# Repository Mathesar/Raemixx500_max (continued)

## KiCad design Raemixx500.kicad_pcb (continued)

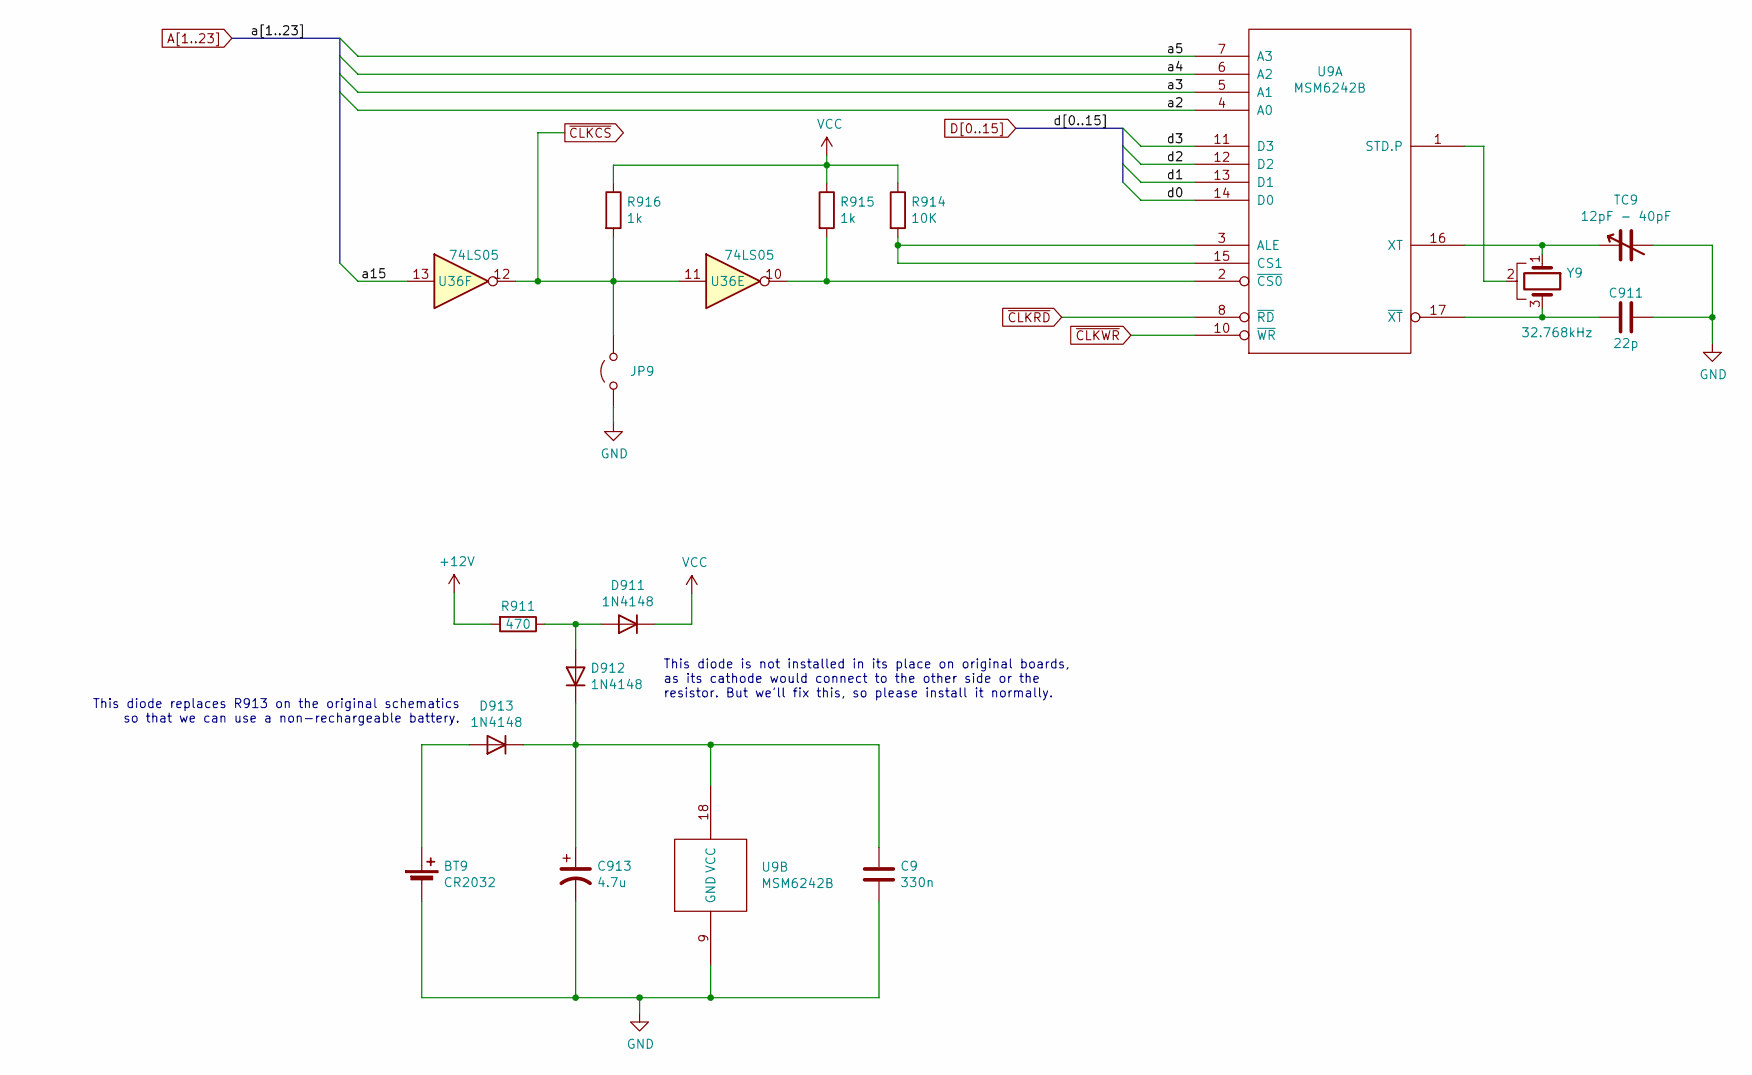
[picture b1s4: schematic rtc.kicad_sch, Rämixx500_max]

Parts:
BT9: CR2032; Battery_Holder_Coin_2032_BS-7; MFG Part Num 122-2420-GR; Mouser 122-2420-GR
C9: 330n; C_Axial_L6.3mm_D2.5mm_P10.16mm; MFG Part Num C440C334K5R5TA7200; Mouser 80-C440C334K5R-TR
C911: 22p; C_Axial_L6.3mm_D2.5mm_P10.16mm; MFG Part Num C410C220J1G5TA; Mouser 80-C410C220J1G
C913: 4.7u; CP_Radial_D8.0mm_P5.00mm; MFG Part Num ECA-2AM4R7B; Mouser 667-ECA-2AM4R7B
D911, D912, D913: 1N4148; D_DO-35_SOD27_P12.70mm_Horizontal; MFG Part Num 1N4148TR; Mouser 512-1N4148TR
JP9: Jumper_2_Open; Jumper2-Open; MFG Part Num SKIP
R911: 470; R_Axial_DIN0309_L9.0mm_D3.2mm_P12.70mm_Horizontal; MFG Part Num MFR-25FBF52-470R; Mouser 603-MFR-25FBF52-470R
R914: 10K; R_Axial_DIN0309_L9.0mm_D3.2mm_P12.70mm_Horizontal; MFG Part Num MFR-25FBF52-10K; Mouser 603-MFR-25FBF52-10K
R915, R916: 1k; R_Axial_DIN0309_L9.0mm_D3.2mm_P12.70mm_Horizontal; MFG Part Num MFR-25FBF52-1K; Mouser 603-MFR-25FBF52-1K
TC9: 12pF - 40pF; VariCap; MFG Part Num JML06-1 / 40PF / YELLOW
U9: MSM6242B; DIP-18_W7.62mm_Socket_LongPads; MFG Part Num 4818-3000-CP; Mouser 517-4818-3000-CP
U36: 74LS05; DIP-14_W7.62mm_LongPads; MFG Part Num SN74LS05N; Mouser 595-SN74LS05N
Y9: 32.768kHz; Crystal_RTC; MFG Part Num ECS-.327-12.5-13X; Mouser 520-TFC2X6-X

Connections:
+12V: R911.2; also elsewhere on the board
A2: U9.4 (A0); also elsewhere on the board
A3: U9.5 (A1); also elsewhere on the board
A4: U9.6 (A2); also elsewhere on the board
A5: U9.7 (A3); also elsewhere on the board
A15: U36.13; also elsewhere on the board
D0: U9.14 (D0); also elsewhere on the board
D1: U9.13 (D1); also elsewhere on the board
D2: U9.12 (D2); also elsewhere on the board
D3: U9.11 (D3); also elsewhere on the board
GND: BT9.2 (-), C9.2, C911.1, C913.2, JP9.1 (A), TC9.2, U9.9 (GND); also elsewhere on the board
unnamed: BT9.1 (+), D913.2 (A)
unnamed: D911.2 (A), D912.2 (A), R911.1
unnamed: C9.1, C913.1, D912.1 (K), D913.1 (K), U9.18 (VCC)
unnamed: R914.2, U9.3 (ALE), U9.15 (CS1)
unnamed: U9.1 (STD.P), Y9.2
unnamed: TC9.1, U9.16 (XT), Y9.1
unnamed: R915.2, U9.2 (~CS0), U36.10
unnamed: C911.2, U9.17 (~XT), Y9.3
VCC: D911.1 (K), R914.1, R915.1, R916.1; also elsewhere on the board
~CLKCS: JP9.2 (B), R916.2, U36.11, U36.12; also elsewhere on the board
~CLKRD: U9.8 (~RD); also elsewhere on the board
~CLKWR: U9.10 (~WR); also elsewhere on the board

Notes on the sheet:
This diode is not installed in its place on original boards, as its cathode would connect to the other side or the resistor. But we'll fix this, so please install it normally.
This diode replaces R913 on the original schematics so that we can use a non-rechargeable battery.

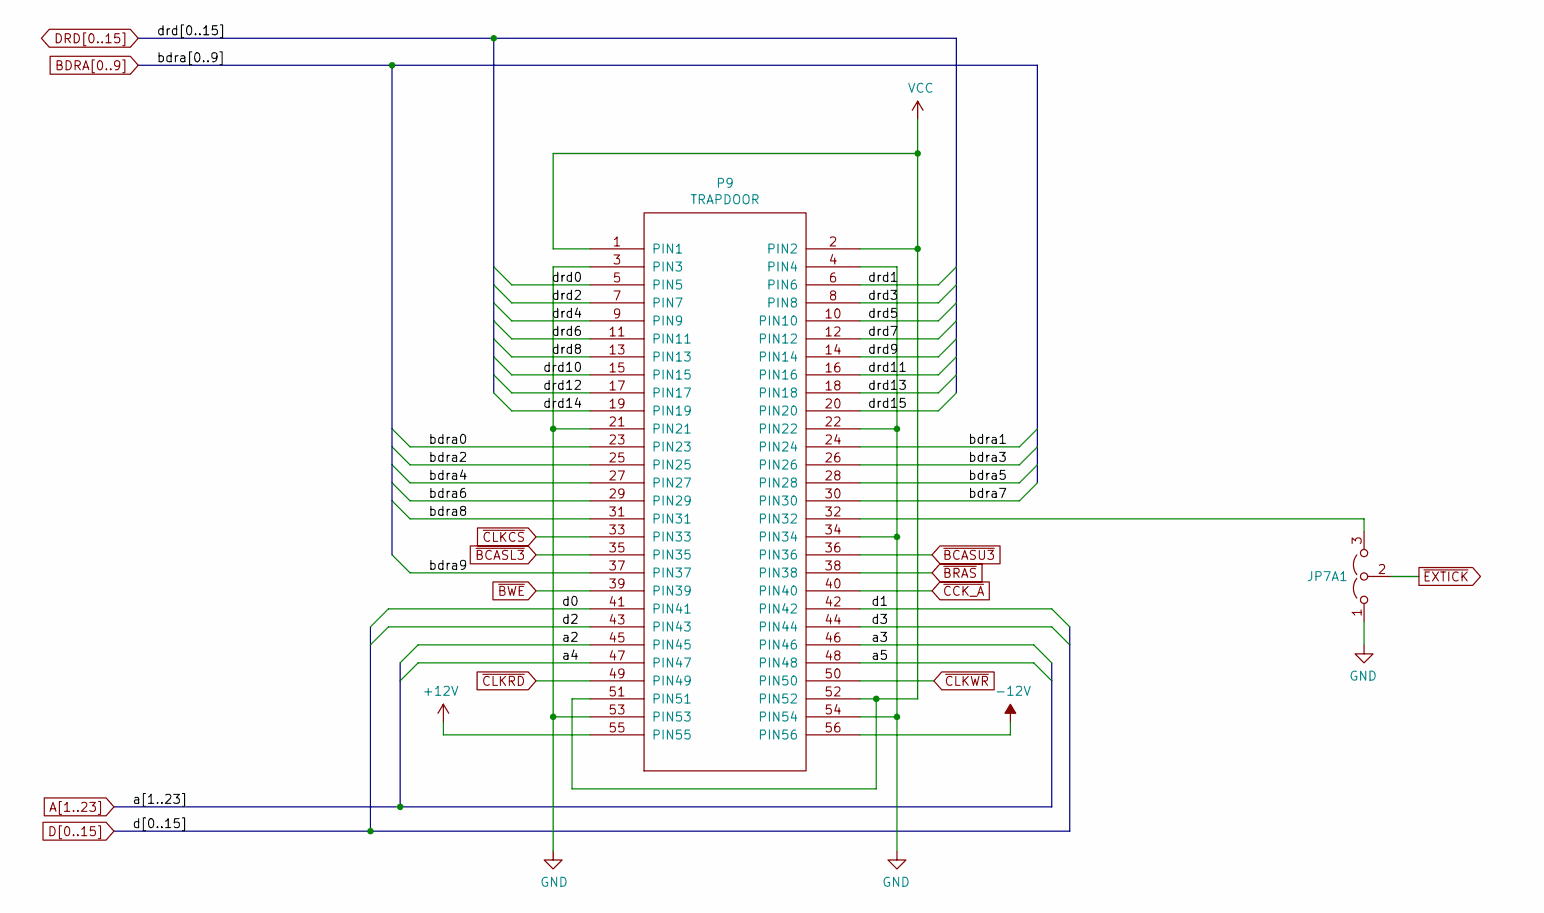
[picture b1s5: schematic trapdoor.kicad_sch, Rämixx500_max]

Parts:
JP7A1: Jumper_3_Open; Jumper3-Open; MFG Part Num SKIP
P9: TRAPDOOR; Trapdoor; MFG Part Num PH2RA-80-UA; Mouser 737-PH2RA-80-UA

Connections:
+12V: P9.55 (PIN55); also elsewhere on the board
-12V: P9.56 (PIN56); also elsewhere on the board
A2: P9.45 (PIN45); also elsewhere on the board
A3: P9.46 (PIN46); also elsewhere on the board
A4: P9.47 (PIN47); also elsewhere on the board
A5: P9.48 (PIN48); also elsewhere on the board
BDRA0: P9.23 (PIN23); also elsewhere on the board
BDRA1: P9.24 (PIN24); also elsewhere on the board
BDRA2: P9.25 (PIN25); also elsewhere on the board
BDRA3: P9.26 (PIN26); also elsewhere on the board
BDRA4: P9.27 (PIN27); also elsewhere on the board
BDRA5: P9.28 (PIN28); also elsewhere on the board
BDRA6: P9.29 (PIN29); also elsewhere on the board
BDRA7: P9.30 (PIN30); also elsewhere on the board
BDRA8: P9.31 (PIN31); also elsewhere on the board
BDRA9: P9.37 (PIN37); also elsewhere on the board
D0: P9.41 (PIN41); also elsewhere on the board
D1: P9.42 (PIN42); also elsewhere on the board
D2: P9.43 (PIN43); also elsewhere on the board
D3: P9.44 (PIN44); also elsewhere on the board
DRD0: P9.5 (PIN5); also elsewhere on the board
DRD1: P9.6 (PIN6); also elsewhere on the board
DRD2: P9.7 (PIN7); also elsewhere on the board
DRD3: P9.8 (PIN8); also elsewhere on the board
DRD4: P9.9 (PIN9); also elsewhere on the board
DRD5: P9.10 (PIN10); also elsewhere on the board
DRD6: P9.11 (PIN11); also elsewhere on the board
DRD7: P9.12 (PIN12); also elsewhere on the board
DRD8: P9.13 (PIN13); also elsewhere on the board
DRD9: P9.14 (PIN14); also elsewhere on the board
DRD10: P9.15 (PIN15); also elsewhere on the board
DRD11: P9.16 (PIN16); also elsewhere on the board
DRD12: P9.17 (PIN17); also elsewhere on the board
DRD13: P9.18 (PIN18); also elsewhere on the board
DRD14: P9.19 (PIN19); also elsewhere on the board
DRD15: P9.20 (PIN20); also elsewhere on the board
GND: JP7A1.1 (A), P9.3 (PIN3), P9.4 (PIN4), P9.21 (PIN21), P9.22 (PIN22), P9.34 (PIN34), P9.53 (PIN53), P9.54 (PIN54); also elsewhere on the board
unnamed: JP7A1.3 (B), P9.32 (PIN32)
VCC: P9.1 (PIN1), P9.2 (PIN2), P9.51 (PIN51), P9.52 (PIN52); also elsewhere on the board
~BCASL3: P9.35 (PIN35); also elsewhere on the board
~BCASU3: P9.36 (PIN36); also elsewhere on the board
~BRAS: P9.38 (PIN38); also elsewhere on the board
~BWE: P9.39 (PIN39); also elsewhere on the board
~CCK_A: P9.40 (PIN40); also elsewhere on the board
~CLKCS: P9.33 (PIN33); also elsewhere on the board
~CLKRD: P9.49 (PIN49); also elsewhere on the board
~CLKWR: P9.50 (PIN50); also elsewhere on the board
~EXTICK: JP7A1.2 (C); also elsewhere on the board

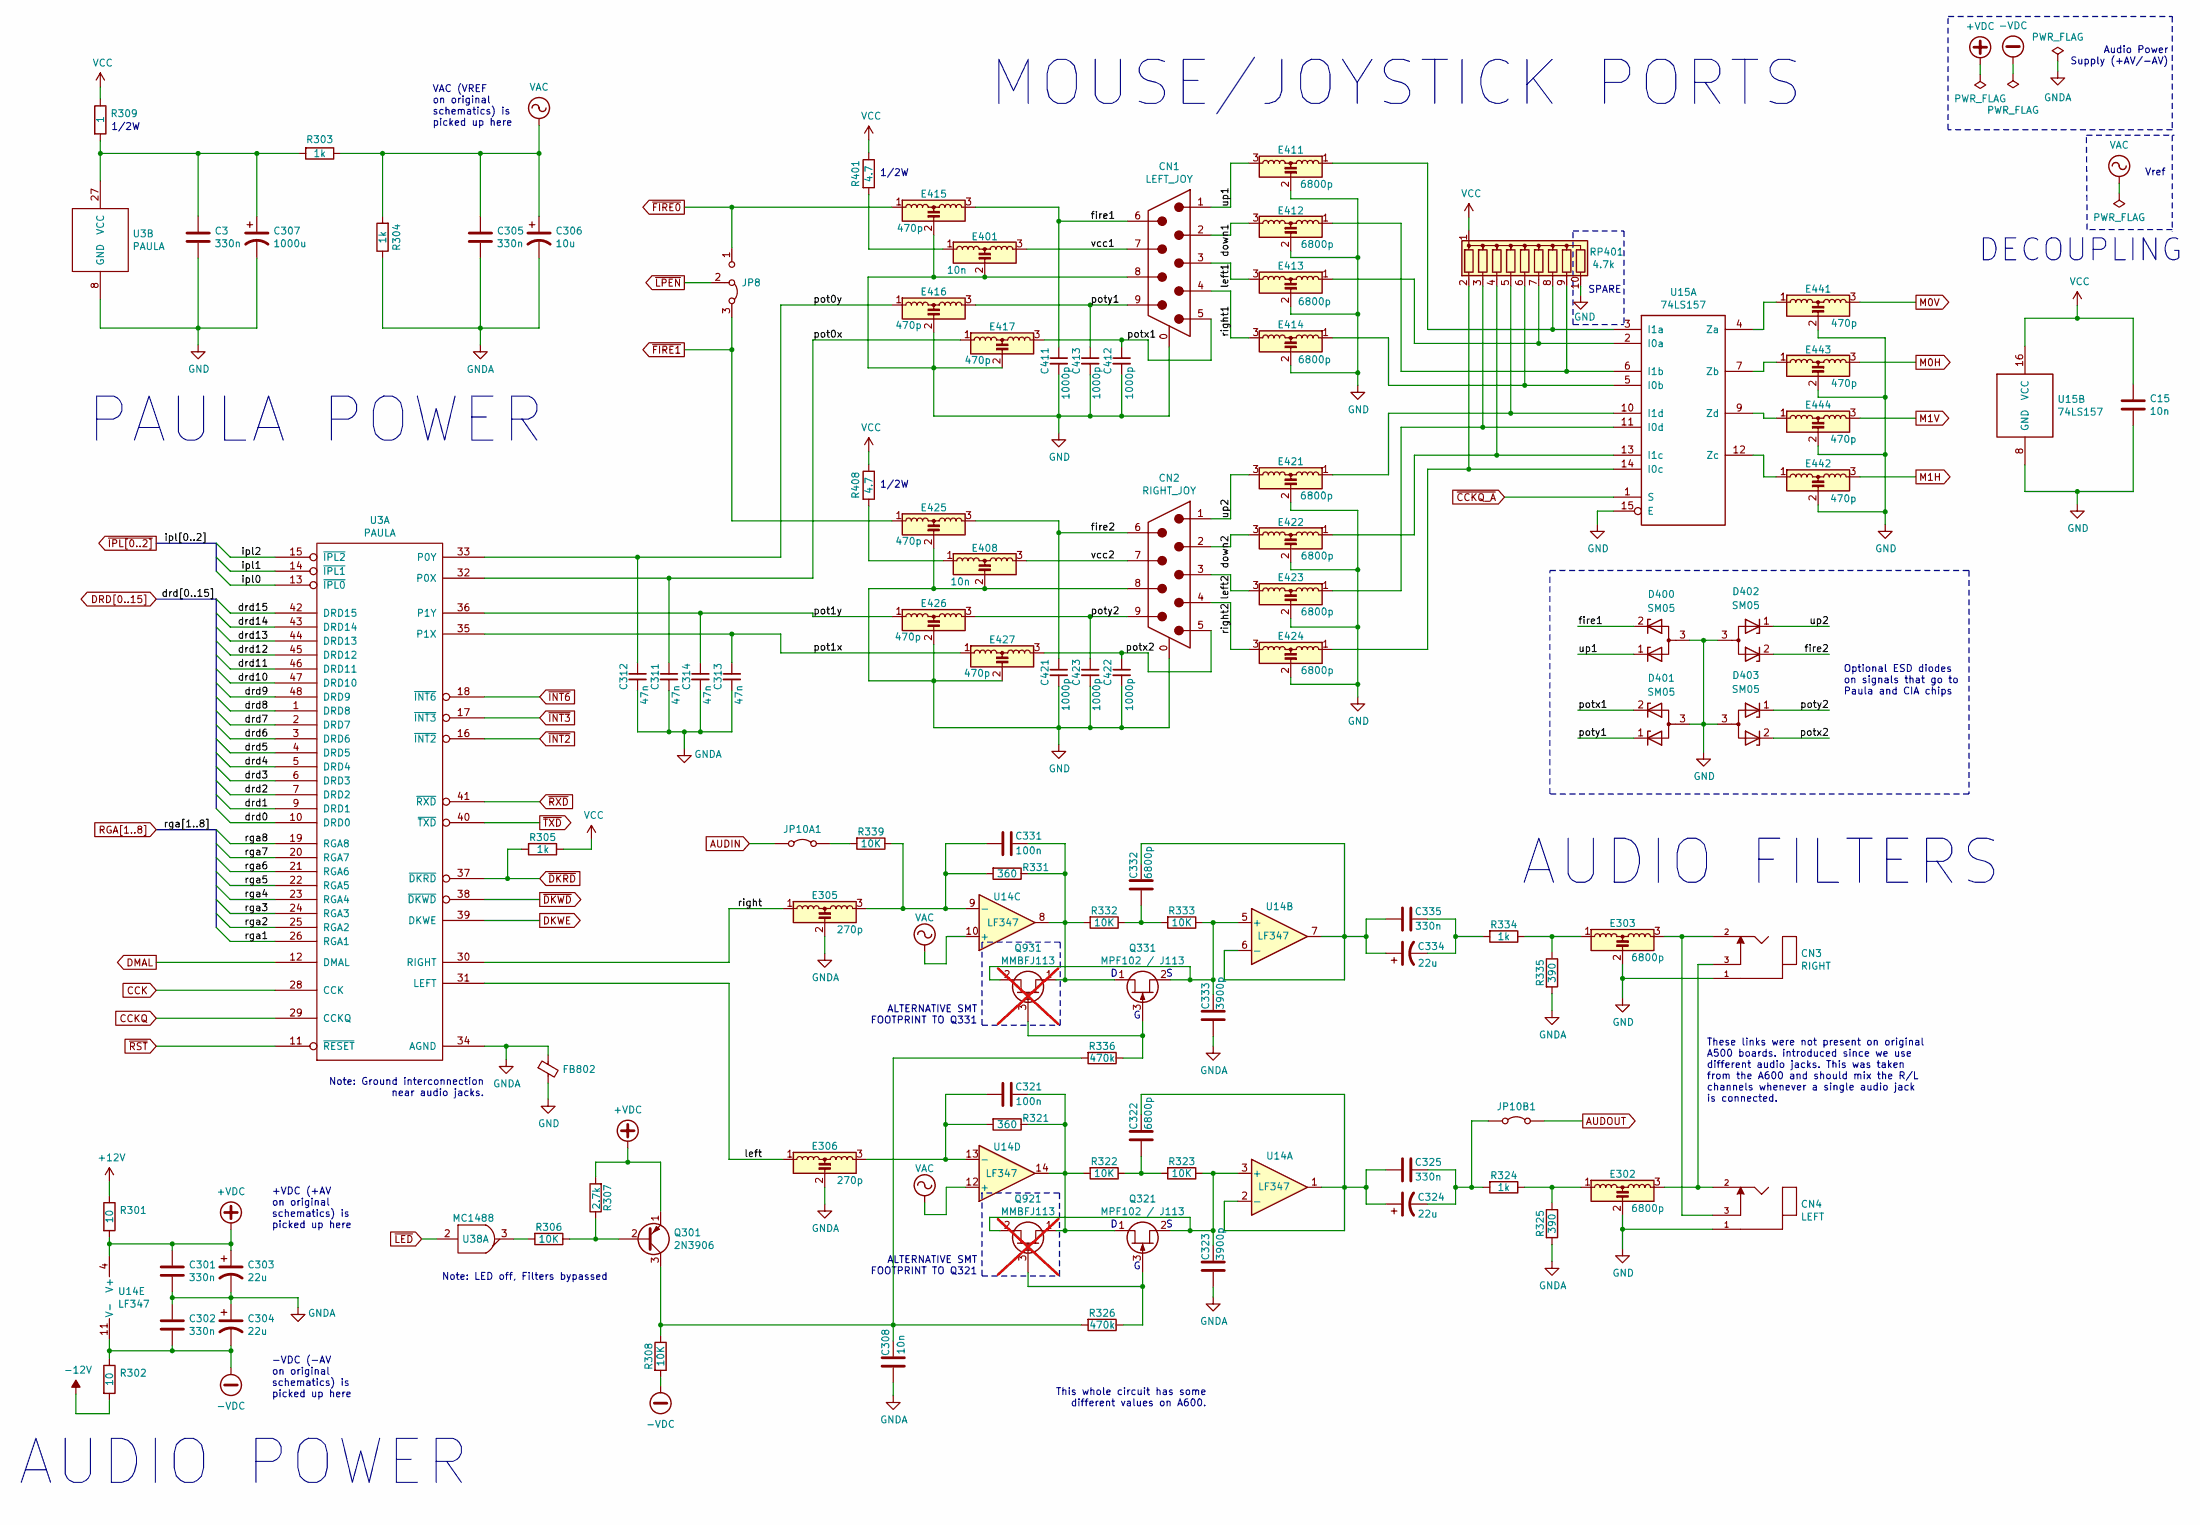
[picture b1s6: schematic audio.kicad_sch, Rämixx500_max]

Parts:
C3: 330n; C_Axial_L6.3mm_D2.5mm_P10.16mm; MFG Part Num C440C334K5R5TA7200; Mouser 80-C440C334K5R-TR
C15: 10n; C_Axial_L6.3mm_D2.5mm_P10.16mm; MFG Part Num C410C103K1R5TA; Mouser 80-C410C103K1R
C301, C302, C305, C325, C335: 330n; C_Axial_L9.0mm_D3.2mm_P12.70mm; MFG Part Num C440C334K5R5TA7200; Mouser 80-C440C334K5R-TR
C303, C304: 22u; CP_Radial_D5.0mm_P2.50mm; MFG Part Num ECA-1EM220I; Mouser 667-ECA-1EM220I
C306: 10u; CP_Radial_D5.0mm_P2.50mm; MFG Part Num ECA-1EM100I; Mouser 667-ECA-1EM100I
C307: 1000u; CP_Radial_D12.5mm_P5.00mm; MFG Part Num ECA-1EM102; Mouser 667-ECA-1EM102
C308: 10n; C_Axial_L9.0mm_D3.2mm_P12.70mm; MFG Part Num C410C103K1R5TA; Mouser 80-C410C103K1R
C311, C312, C313, C314: 47n; C_Axial_L9.0mm_D3.2mm_P12.70mm; MFG Part Num C410C473M5R5TA7200; Mouser 80-C410C473M5R-TR
C321, C331: 100n; C_Axial_L9.0mm_D3.2mm_P12.70mm; MFG Part Num A104K15X7RF5TAA; Mouser 594-A104K15X7RF5TAA
C322, C332: 6800p; C_Axial_L9.0mm_D3.2mm_P12.70mm; MFG Part Num C410C682K2R5TA7200; Mouser 80-C410C682K2R5TATU
C323, C333: 3900p; C_Axial_L9.0mm_D3.2mm_P12.70mm; MFG Part Num C410C392K1R5TA; Mouser 80-C410C392K1R
C324, C334: 22u; CP_Radial_D8.0mm_P5.00mm; MFG Part Num ECA-1EM220B; Mouser 667-ECA-1EM220B
C411, C412, C413, C421, C422, C423: 1000p; C_Axial_L9.0mm_D3.2mm_P12.70mm; MFG Part Num C410C102M5R5TA7200; Mouser 80-C410C102M5R-TR
CN1: LEFT_JOY; DB_9M; MFG Part Num L17HTNEP4F1C; Mouser 523-L17HTNEP4F1C
CN2: RIGHT_JOY; DB_9M; MFG Part Num L17HTNEP4F1C; Mouser 523-L17HTNEP4F1C
CN3: RIGHT; SWITCHCRAFT_PJRAN1X1U01X; MFG Part Num PJRAN1X1U01AUX; Mouser 502-PJRAN1X1U01AUX
CN4: LEFT; SWITCHCRAFT_PJRAN1X1U01X; MFG Part Num PJRAN1X1U01AUX; Mouser 502-PJRAN1X1U01AUX
D400, D401, D402, D403: SM05; SOT-23_Handsoldering_NoSilk; MFG Part Num SM05-7; Mouser 621-SM05-7
E302, E303: 6800p; EMI_Filter_Short; MFG Part Num DSS1NB32A682Q91A; Mouser 81-DSS1NB32A682Q91A
E305, E306: 270p; EMI_Filter_Long; MFG Part Num DSS1NB32A271Q91A; Mouser 81-DSS1NB32A271Q91A
E401, E408: 10n; EMI_Filter_Long; MFG Part Num DSS1NB32A103Q91A; Mouser 81-DSS1NB32A103Q91A
E411, E412, E413, E414, E421, E422, E423, E424: 6800p; EMI_Filter_Long; MFG Part Num DSS1NB32A682Q91A; Mouser 81-DSS1NB32A682Q91A
E415, E416, E417, E425, E426, E427, E441, E442, E443, E444: 470p; EMI_Filter_Long; MFG Part Num DSS1NB32A471Q91A; Mouser 81-DSS1NB32A471Q91A
FB802: Ferrite_Bead_Small; Ferrite_Axial_L9.0mm_D3.2mm_P12.70mm; MFG Part Num 2743007111; Mouser 623-2743007111
JP8: Jumper_3_Bridged23; Jumper3-Bridged23; MFG Part Num SKIP
JP10A1, JP10B1: Jumper_2_Bridged; Jumper2-Bridged; MFG Part Num SKIP
Q301: 2N3906; TO-92L_Inline_Wide; MFG Part Num 2N3906BU; Mouser 512-2N3906BU
Q321, Q331: MPF102 / J113; TO-92L_Inline_Wide; MFG Part Num J113; Mouser 512-J113
Q921, Q931: MMBFJ113; SOT-23_LongerPads; not fitted
R301, R302: 10; R_Axial_DIN0309_L9.0mm_D3.2mm_P12.70mm_Horizontal; MFG Part Num MFR-25FBF52-10R; Mouser 603-MFR-25FBF52-10R
R303, R304, R305, R324, R334: 1k; R_Axial_DIN0309_L9.0mm_D3.2mm_P12.70mm_Horizontal; MFG Part Num MFR-25FBF52-1K; Mouser 603-MFR-25FBF52-1K
R306, R308, R322, R323, R332, R333, R339: 10K; R_Axial_DIN0309_L9.0mm_D3.2mm_P12.70mm_Horizontal; MFG Part Num MFR-25FBF52-10K; Mouser 603-MFR-25FBF52-10K
R307: 2.7k; R_Axial_DIN0309_L9.0mm_D3.2mm_P12.70mm_Horizontal; MFG Part Num MFR-25FBF52-2K7; Mouser 603-MFR-25FBF52-2K7
R309: 1; R_Axial_DIN0309_L9.0mm_D3.2mm_P15.24mm_Horizontal; MFG Part Num PR01000101008JA500; Mouser 594-PR01000101008JA5
R321, R331: 360; R_Axial_DIN0309_L9.0mm_D3.2mm_P12.70mm_Horizontal; MFG Part Num MFR-25FRF52-360R; Mouser 603-MFR-25FRF52-360R
R325, R335: 390; R_Axial_DIN0309_L9.0mm_D3.2mm_P12.70mm_Horizontal; MFG Part Num MFR-25FBF52-390R; Mouser 603-MFR-25FBF52-390R
R326, R336: 470k; R_Axial_DIN0309_L9.0mm_D3.2mm_P12.70mm_Horizontal; MFG Part Num MFR-25FBF52-470K; Mouser 603-MFR-25FBF52-470K
R401, R408: 4.7; R_Axial_DIN0309_L9.0mm_D3.2mm_P15.24mm_Horizontal; MFG Part Num PR01000104708JA500; Mouser 594-PR01000104708JA5
RP401: 4.7k; R_Array_SIP10; MFG Part Num 4610X-101-472LF; Mouser 652-4610X-1LF-4.7K
U3: PAULA; DIP-48_W15.24mm_Socket_LongPads; MFG Part Num 4848-6000-CP; Mouser 517-4848-6000-CP
U14: LF347; DIP-14_W7.62mm_LongPads; MFG Part Num LF347N; Mouser 595-LF347N
U15: 74LS157; DIP-16_W7.62mm_LongPads; MFG Part Num SN74LS157N; Mouser 595-SN74LS157N
U38: MC1488; DIP-14_W7.62mm_LongPads; MFG Part Num SN75C188N; Mouser 595-SN75C188N

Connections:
+12V: R301.1; also elsewhere on the board
+VDC: C301.1, C303.1, Q301.1 (E), R301.2, R307.2, U14.4 (V+)
-12V: R302.2; also elsewhere on the board
-VDC: C302.2, C304.2, R302.1, R308.2, U14.11 (V-)
/Paula & Audio Stuff/down1: CN1.2, E412.3
/Paula & Audio Stuff/down2: CN2.2, E422.3
/Paula & Audio Stuff/fire1: C411.1, CN1.6, D400.2 (K), E415.3
/Paula & Audio Stuff/fire2: C421.1, CN2.6, D402.2 (K), E425.3
/Paula & Audio Stuff/left: E306.1, U3.31 (LEFT)
/Paula & Audio Stuff/left1: CN1.3, E413.3
/Paula & Audio Stuff/left2: CN2.3, E423.3
/Paula & Audio Stuff/pot0x: C311.1, E417.1, U3.32 (P0X)
/Paula & Audio Stuff/pot0y: C312.1, E416.1, U3.33 (P0Y)
/Paula & Audio Stuff/pot1x: C313.1, E427.1, U3.35 (P1X)
/Paula & Audio Stuff/pot1y: C314.1, E426.1, U3.36 (P1Y)
/Paula & Audio Stuff/potx1: C412.1, CN1.5, D401.2 (K), E417.3
/Paula & Audio Stuff/potx2: C422.1, CN2.5, D403.2 (K), E427.3
/Paula & Audio Stuff/poty1: C413.1, CN1.9, D401.1 (K), E416.3
/Paula & Audio Stuff/poty2: C423.1, CN2.9, D403.1 (K), E426.3
/Paula & Audio Stuff/right: E305.1, U3.30 (RIGHT)
/Paula & Audio Stuff/right1: CN1.4, E414.3
/Paula & Audio Stuff/right2: CN2.4, E424.3
/Paula & Audio Stuff/up1: CN1.1, D400.1 (K), E411.3
/Paula & Audio Stuff/up2: CN2.1, D402.1 (K), E421.3
/Paula & Audio Stuff/vcc1: CN1.7, E401.3
/Paula & Audio Stuff/vcc2: CN2.7, E408.3
AUDIN: JP10A1.1 (A); also elsewhere on the board
AUDOUT: JP10B1.2 (B); also elsewhere on the board
CCK: U3.28 (CCK); also elsewhere on the board
CCKQ: U3.29 (CCKQ); also elsewhere on the board
DKWE: U3.39 (DKWE); also elsewhere on the board
DMAL: U3.12 (DMAL); also elsewhere on the board
DRD0: U3.10 (DRD0); also elsewhere on the board
DRD1: U3.9 (DRD1); also elsewhere on the board
DRD2: U3.7 (DRD2); also elsewhere on the board
DRD3: U3.6 (DRD3); also elsewhere on the board
DRD4: U3.5 (DRD4); also elsewhere on the board
DRD5: U3.4 (DRD5); also elsewhere on the board
DRD6: U3.3 (DRD6); also elsewhere on the board
DRD7: U3.2 (DRD7); also elsewhere on the board
DRD8: U3.1 (DRD8); also elsewhere on the board
DRD9: U3.48 (DRD9); also elsewhere on the board
DRD10: U3.47 (DRD10); also elsewhere on the board
DRD11: U3.46 (DRD11); also elsewhere on the board
DRD12: U3.45 (DRD12); also elsewhere on the board
DRD13: U3.44 (DRD13); also elsewhere on the board
DRD14: U3.43 (DRD14); also elsewhere on the board
DRD15: U3.42 (DRD15); also elsewhere on the board
GND: C3.2, C15.2, C307.2, C411.2, C412.2, C413.2, C421.2, C422.2, C423.2, CN1.0 (PAD), CN1.8, CN2.0 (PAD), CN2.8, CN3.1, CN4.1, D400.3 (A), D401.3 (A), D402.3 (A), D403.3 (A), E302.2, E303.2, E401.2, E408.2, E411.2, E412.2, E413.2, E414.2, E415.2, E416.2, E417.2, E421.2, E422.2, E423.2, E424.2, E425.2, E426.2, E427.2, E441.2, E442.2, E443.2, E444.2, FB802.2, RP401.10 (R9), U3.8 (GND), U15.8 (GND), U15.15 (E); also elsewhere on the board
GNDA: C301.2, C302.1, C303.2, C304.1, C305.2, C306.2, C308.2, C311.2, C312.2, C313.2, C314.2, C323.2, C333.2, E305.2, E306.2, FB802.1, R304.1, R325.2, R335.2, U3.34 (AGND)
M0H: E443.3; also elsewhere on the board
M0V: E441.3; also elsewhere on the board
M1H: E442.3; also elsewhere on the board
M1V: E444.3; also elsewhere on the board
unnamed: C322.2, R322.1, R323.2
unnamed: C332.2, R332.1, R333.2
unnamed: C334.2, C335.1, R334.2
unnamed: CN3.2, CN4.3, E303.3
unnamed: CN3.3, CN4.2, E302.3
unnamed: E302.1, R324.1, R325.1
unnamed: E303.1, R334.1, R335.1
unnamed: E401.1, R401.2
unnamed: E408.1, R408.2
unnamed: JP10A1.2 (B), R339.2
unnamed: C324.2, C325.1, JP10B1.1 (A), R324.2
unnamed: Q301.2 (B), R306.1, R307.1
unnamed: C308.1, Q301.3 (C), R308.1, R326.2, R336.2
unnamed: C321.1, Q321.1 (D), Q921.1 (D), R321.1, R322.2, U14.14
unnamed: Q321.3 (G), Q921.3 (G), R326.1
unnamed: C323.1, Q321.2 (S), Q921.2 (S), R323.1, U14.3 (+)
unnamed: C331.1, Q331.1 (D), Q931.1 (D), R331.1, R332.2, U14.8
unnamed: Q331.3 (G), Q931.3 (G), R336.1
unnamed: C333.1, Q331.2 (S), Q931.2 (S), R333.1, U14.5 (+)
unnamed: R306.2, U38.3
unnamed: E424.1, RP401.2 (R1), U15.14 (I0c)
unnamed: E423.1, RP401.3 (R2), U15.11 (I0d)
unnamed: E422.1, RP401.4 (R3), U15.13 (I1c)
unnamed: E421.1, RP401.5 (R4), U15.10 (I1d)
unnamed: E414.1, RP401.6 (R5), U15.5 (I0b)
unnamed: E413.1, RP401.7 (R6), U15.2 (I0a)
unnamed: E411.1, RP401.8 (R7), U15.3 (I1a)
unnamed: E412.1, RP401.9 (R8), U15.6 (I1b)
unnamed: C3.1, C307.1, R303.2, R309.2, U3.27 (VCC)
unnamed: C322.1, C324.1, C325.2, U14.1, U14.2 (-)
unnamed: C332.1, C334.1, C335.2, U14.6 (-), U14.7
unnamed: C331.2, E305.3, R331.2, R339.1, U14.9 (-)
unnamed: C321.2, E306.3, R321.2, U14.13 (-)
unnamed: E441.1, U15.4 (Za)
unnamed: E443.1, U15.7 (Zb)
unnamed: E442.1, U15.12 (Zc)
unnamed: E444.1, U15.9 (Zd)
RGA1: U3.26 (RGA1); also elsewhere on the board
RGA2: U3.25 (RGA2); also elsewhere on the board
RGA3: U3.24 (RGA3); also elsewhere on the board
RGA4: U3.23 (RGA4); also elsewhere on the board
RGA5: U3.22 (RGA5); also elsewhere on the board
RGA6: U3.21 (RGA6); also elsewhere on the board
RGA7: U3.20 (RGA7); also elsewhere on the board
RGA8: U3.19 (RGA8); also elsewhere on the board
VAC: C305.1, C306.1, R303.1, R304.2, U14.10 (+), U14.12 (+)
VCC: C15.1, R305.1, R309.1, R401.1, R408.1, RP401.1 (common), U15.16 (VCC); also elsewhere on the board
~CCKQ_A: U15.1 (S); also elsewhere on the board
~DKRD: R305.2, U3.37 (~DKRD); also elsewhere on the board
~DKWD: U3.38 (~DKWD); also elsewhere on the board
~FIRE0: E415.1, JP8.1 (A); also elsewhere on the board
~FIRE1: E425.1, JP8.3 (B); also elsewhere on the board
~INT2: U3.16 (~INT2); also elsewhere on the board
~INT3: U3.17 (~INT3); also elsewhere on the board
~INT6: U3.18 (~INT6); also elsewhere on the board
~IPL0: U3.13 (~IPL0); also elsewhere on the board
~IPL1: U3.14 (~IPL1); also elsewhere on the board
~IPL2: U3.15 (~IPL2); also elsewhere on the board
~LED: U38.2; also elsewhere on the board
~LPEN: JP8.2 (C); also elsewhere on the board
~RST: U3.11 (~RESET); also elsewhere on the board
~RXD: U3.41 (~RXD); also elsewhere on the board
~TXD: U3.40 (~TXD); also elsewhere on the board

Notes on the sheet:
DECOUPLING
Optional ESD diodes on signals that go to Paula and CIA chips
Note: LED off, Filters bypassed
AUDIO POWER
ALTERNATIVE SMT FOOTPRINT TO Q331
Vref
1/2W
VAC (VREF on original schematics) is picked up here
These links were not present on original A500 boards. introduced since we use different audio jacks. This was taken from the A600 and should mix the R/L channels whenever a single audio jack is connected.
Audio Power Supply (+AV/-AV)
SPARE
+VDC (+AV on original schematics) is picked up here
-VDC (-AV on original schematics) is picked up here
This whole circuit has some different values on A600.
PAULA POWER
AUDIO FILTERS
ALTERNATIVE SMT FOOTPRINT TO Q321
MOUSE/JOYSTICK PORTS
Note: Ground interconnection near audio jacks.

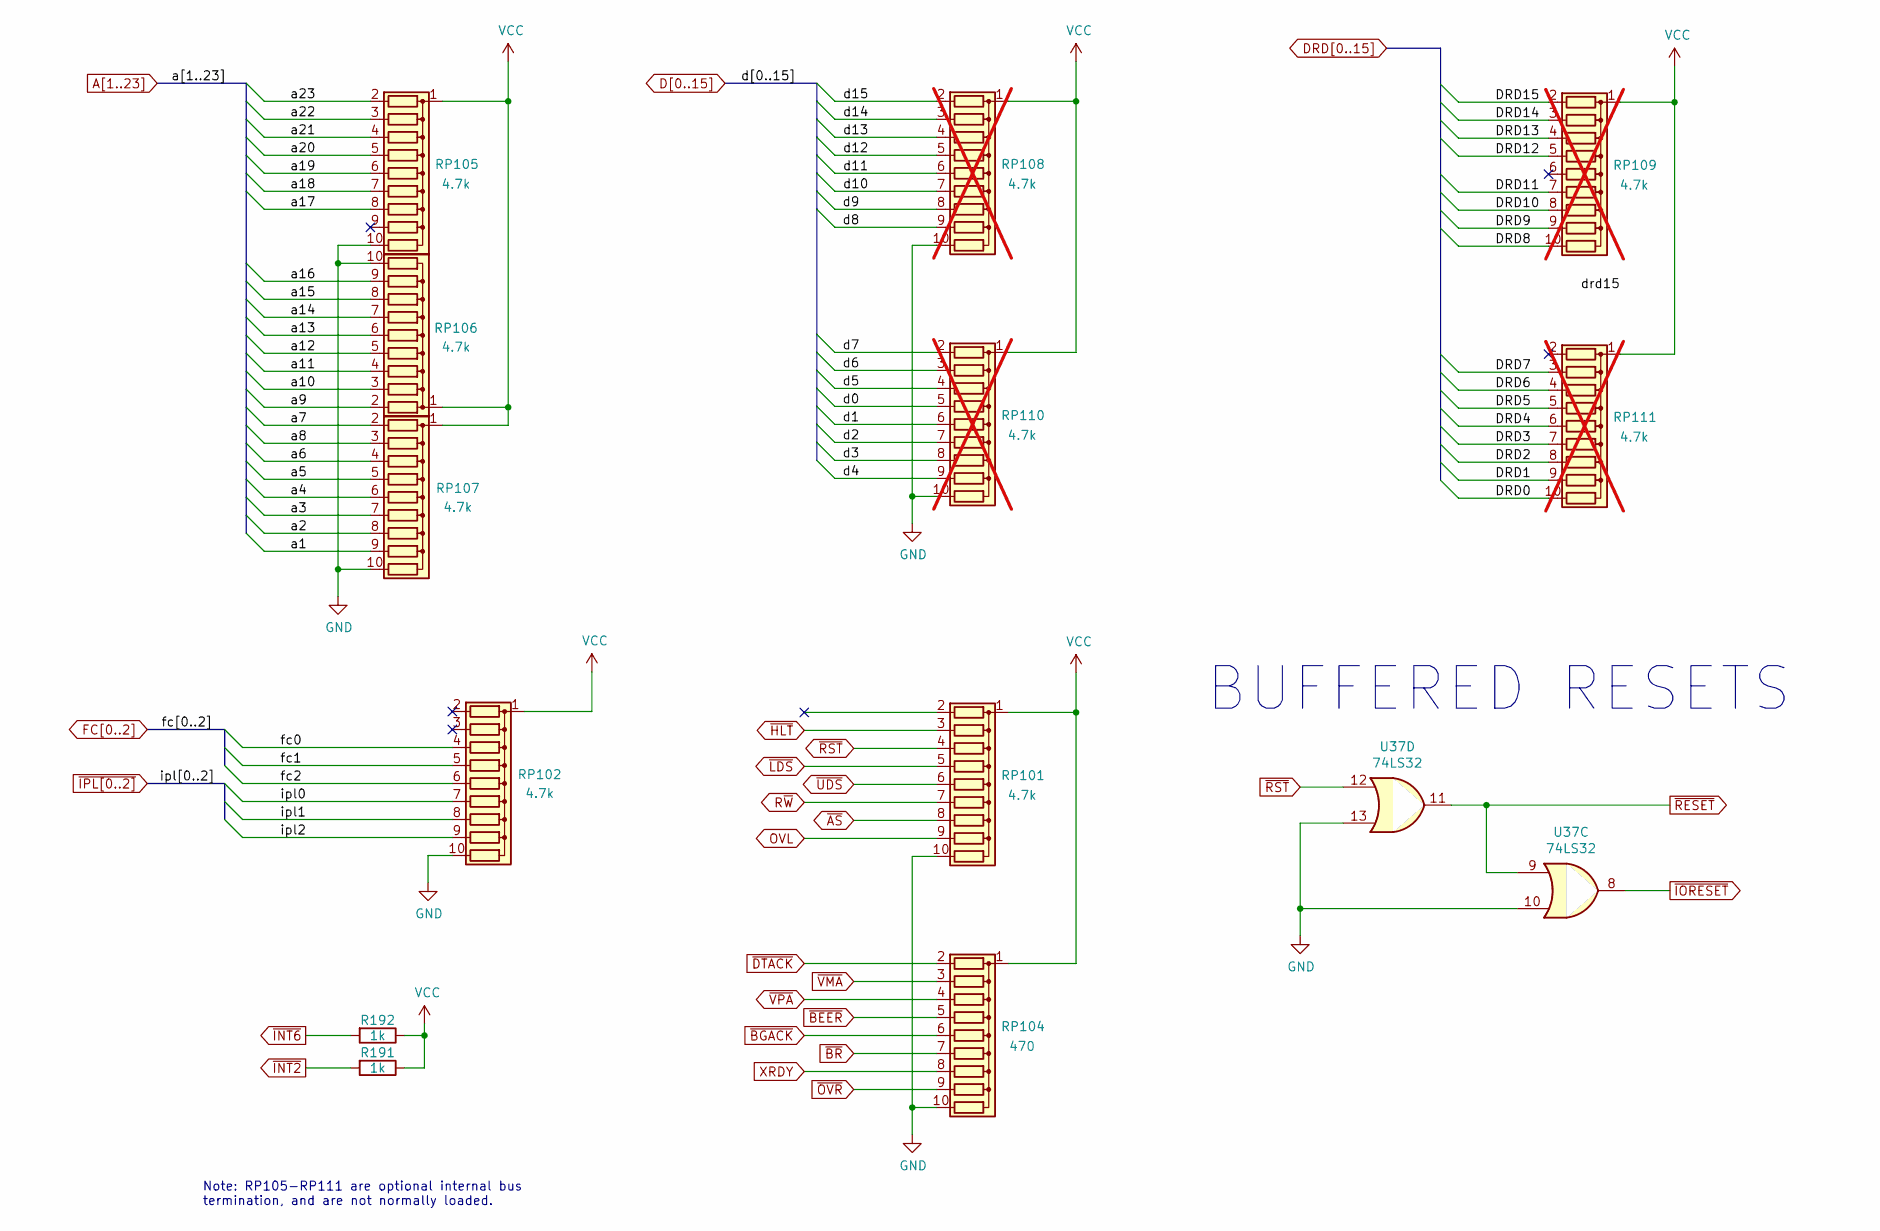
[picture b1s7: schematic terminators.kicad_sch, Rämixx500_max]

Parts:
R191, R192: 1k; R_Axial_DIN0309_L9.0mm_D3.2mm_P12.70mm_Horizontal; MFG Part Num MFR-25FBF52-1K; Mouser 603-MFR-25FBF52-1K
RP101, RP102, RP105, RP106, RP107: 4.7k; R_Array_SIP10; MFG Part Num 4610X-101-472LF; Mouser 652-4610X-1LF-4.7K
RP104: 470; R_Array_SIP10; MFG Part Num 4610X-101-471LF; Mouser 652-4610X-1LF-470
RP108, RP109, RP110, RP111: 4.7k; R_Array_SIP10; not fitted
U37: 74LS32; DIP-14_W7.62mm_LongPads; MFG Part Num SN74LS32N; Mouser 595-SN74LS32N

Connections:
A1: RP107.9 (R8); also elsewhere on the board
A2: RP107.8 (R7); also elsewhere on the board
A3: RP107.7 (R6); also elsewhere on the board
A4: RP107.6 (R5); also elsewhere on the board
A5: RP107.5 (R4); also elsewhere on the board
A6: RP107.4 (R3); also elsewhere on the board
A7: RP107.2 (R1); also elsewhere on the board
A8: RP107.3 (R2); also elsewhere on the board
A9: RP106.2 (R1); also elsewhere on the board
A10: RP106.3 (R2); also elsewhere on the board
A11: RP106.4 (R3); also elsewhere on the board
A12: RP106.5 (R4); also elsewhere on the board
A13: RP106.6 (R5); also elsewhere on the board
A14: RP106.7 (R6); also elsewhere on the board
A15: RP106.8 (R7); also elsewhere on the board
A16: RP106.9 (R8); also elsewhere on the board
A17: RP105.8 (R7); also elsewhere on the board
A18: RP105.7 (R6); also elsewhere on the board
A19: RP105.6 (R5); also elsewhere on the board
A20: RP105.5 (R4); also elsewhere on the board
A21: RP105.4 (R3); also elsewhere on the board
A22: RP105.3 (R2); also elsewhere on the board
A23: RP105.2 (R1); also elsewhere on the board
D0: RP110.5 (R4); also elsewhere on the board
D1: RP110.6 (R5); also elsewhere on the board
D2: RP110.7 (R6); also elsewhere on the board
D3: RP110.8 (R7); also elsewhere on the board
D4: RP110.9 (R8); also elsewhere on the board
D5: RP110.4 (R3); also elsewhere on the board
D6: RP110.3 (R2); also elsewhere on the board
D7: RP110.2 (R1); also elsewhere on the board
D8: RP108.9 (R8); also elsewhere on the board
D9: RP108.8 (R7); also elsewhere on the board
D10: RP108.7 (R6); also elsewhere on the board
D11: RP108.6 (R5); also elsewhere on the board
D12: RP108.5 (R4); also elsewhere on the board
D13: RP108.4 (R3); also elsewhere on the board
D14: RP108.3 (R2); also elsewhere on the board
D15: RP108.2 (R1); also elsewhere on the board
DRD0: RP111.10 (R9); also elsewhere on the board
DRD1: RP111.9 (R8); also elsewhere on the board
DRD2: RP111.8 (R7); also elsewhere on the board
DRD3: RP111.7 (R6); also elsewhere on the board
DRD4: RP111.6 (R5); also elsewhere on the board
DRD5: RP111.5 (R4); also elsewhere on the board
DRD6: RP111.4 (R3); also elsewhere on the board
DRD7: RP111.3 (R2); also elsewhere on the board
DRD8: RP109.10 (R9); also elsewhere on the board
DRD9: RP109.9 (R8); also elsewhere on the board
DRD10: RP109.8 (R7); also elsewhere on the board
DRD11: RP109.7 (R6); also elsewhere on the board
DRD12: RP109.5 (R4); also elsewhere on the board
DRD13: RP109.4 (R3); also elsewhere on the board
DRD14: RP109.3 (R2); also elsewhere on the board
DRD15: RP109.2 (R1); also elsewhere on the board
FC0: RP102.4 (R3); also elsewhere on the board
FC1: RP102.5 (R4); also elsewhere on the board
FC2: RP102.6 (R5); also elsewhere on the board
GND: RP101.10 (R9), RP102.10 (R9), RP104.10 (R9), RP105.10 (R9), RP106.10 (R9), RP107.10 (R9), RP108.10 (R9), RP110.10 (R9), U37.10, U37.13; also elsewhere on the board
OVL: RP101.9 (R8); also elsewhere on the board
R~W: RP101.7 (R6); also elsewhere on the board
VCC: R191.1, R192.1, RP101.1 (common), RP102.1 (common), RP104.1 (common), RP105.1 (common), RP106.1 (common), RP107.1 (common), RP108.1 (common), RP109.1 (common), RP110.1 (common), RP111.1 (common); also elsewhere on the board
XRDY: RP104.8 (R7); also elsewhere on the board
~AS: RP101.8 (R7); also elsewhere on the board
~BEER: RP104.5 (R4); also elsewhere on the board
~BGACK: RP104.6 (R5); also elsewhere on the board
~BR: RP104.7 (R6); also elsewhere on the board
~DTACK: RP104.2 (R1); also elsewhere on the board
~HLT: RP101.3 (R2); also elsewhere on the board
~INT2: R191.2; also elsewhere on the board
~INT6: R192.2; also elsewhere on the board
~IORESET: U37.8; also elsewhere on the board
~IPL0: RP102.7 (R6); also elsewhere on the board
~IPL1: RP102.8 (R7); also elsewhere on the board
~IPL2: RP102.9 (R8); also elsewhere on the board
~LDS: RP101.5 (R4); also elsewhere on the board
~OVR: RP104.9 (R8); also elsewhere on the board
~RESET: U37.9, U37.11; also elsewhere on the board
~RST: RP101.4 (R3), U37.12; also elsewhere on the board
~UDS: RP101.6 (R5); also elsewhere on the board
~VMA: RP104.3 (R2); also elsewhere on the board
~VPA: RP104.4 (R3); also elsewhere on the board

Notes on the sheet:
Note: RP105-RP111 are optional internal bus termination, and are not normally loaded.
BUFFERED RESETS
